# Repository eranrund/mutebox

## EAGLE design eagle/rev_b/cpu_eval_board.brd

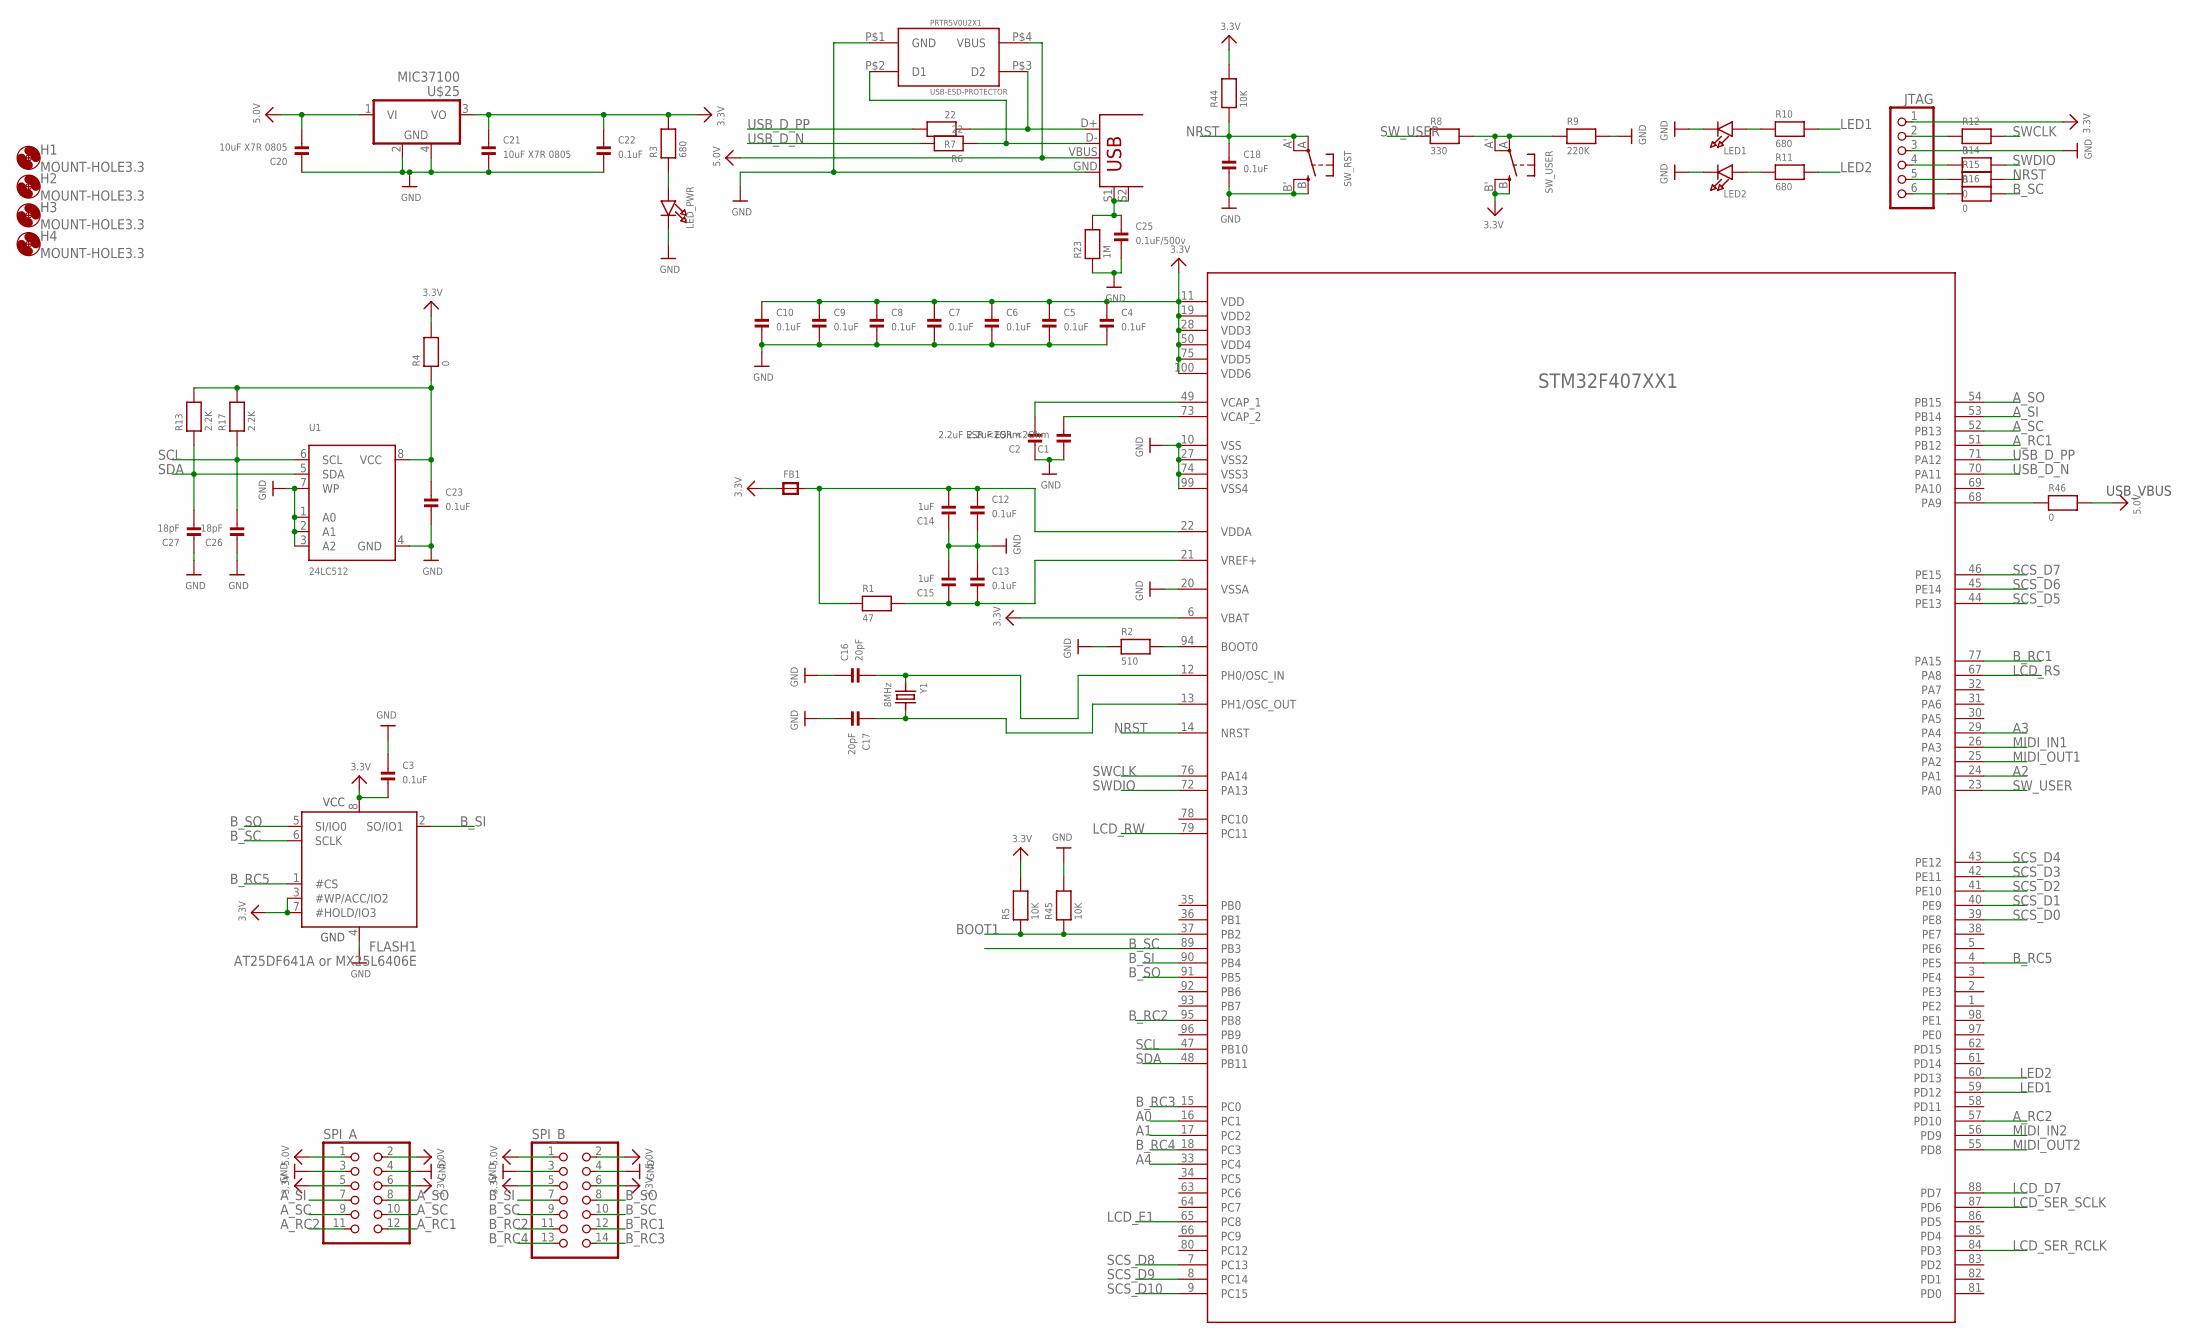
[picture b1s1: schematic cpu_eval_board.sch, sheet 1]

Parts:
C1, C2: 2.2uF ESR <2Ohm; 0603; PARTNO GRM188R61E225KA12D,Murata Electronics,,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
C3, C4, C5, C6, C7, C8, C9, C10, C12, C13, C18, C22, C23: 0.1uF; 0603; PARTNO VJ0603Y104JXJPW1BC,Vishay / Vitramon,,7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
C14, C15: 1uF; 0603; PARTNO GRM188R61E105KA12D,Murata Electronics,,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
C16, C17: 20pF; 0603; PARTNO GRM1885C1H200JA01D,Murata Electronics,,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
C20, C21: 10uF X7R 0805; _0805; PARTNO GRM21BR71A106KA73L,Murata Electronics,,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
C25: 0.1uF/500v; 0603; PARTNO CGA3E3X7S2A104M080AB,TDK,,810-CGA3E3X7S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
C26, C27: 18pF; 0603; PARTNO VJ0603A180JXACW1BC,Vishay / Vitramon,,7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
FB1: FERRITE_0805; _0805; PARTNO HZ0805E601R-10,Laird Technologies,,875-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
FLASH1: AT25DF641A or MX25L6406E; SOIC-8-WIDE
H1, H2, H3, H4: MOUNT-HOLE3.3; 3,3
JTAG: HEADER-1X6ROUND; 1X06_ROUND; PARTNO XG8V-0641,Omron Electronics,,653-XG8V-0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
LED1, LED2: LED0603; CHIPLED_0603; PARTNO VLMS1300-GS08,Vishay Semiconductors,,78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
LED_PWR: LED0603; CHIPLED_0603; PARTNO VLMS1300-GS08,Vishay Semiconductors,,78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
PRTR5V0U2X1: USB-ESD-PROTECTOR; PRTR5V0U2X; PARTNO PRTR5V0U2X,215",NXP Semiconductors,,771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
R1: 47; 0603; PARTNO CRCW060347R0FKEA,Vishay / Dale,,71-CRCW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
R2: 510; 0603; PARTNO RT0603FRE07510RL,Yageo,,603-RT0603FRE07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
R3, R10, R11: 680; 0603; PARTNO MCT06030C6800FP500,Vishay / Beyschlag,,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
R4, R12, R14, R15, R16, R46: 0; 0603; PARTNO MCT06030Z0000ZP500,Vishay / Beyschlag,,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
R5, R44, R45: 10K; 0603; PARTNO CRCW060310K0FKEA,Vishay / Dale,,71-CRCW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
R6, R7: 22; 0603; PARTNO MCT06030C2209FP500,Vishay / Beyschlag,,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
R8: 330; 0603; PARTNO RT0603FRE07330RL,Yageo,,603-RT0603FRE07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
R9: 220K; 0603; PARTNO RT0603FRE07220KL,Yageo,,603-RT0603FRE07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
R13, R17: 2.2K; 0603; PARTNO MCT06030C2201FP500,Vishay / Beyschlag,,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
R23: 1M; 0603; PARTNO CRCW06031M00FKEA,Vishay / Dale,,71-CRCW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
SPI_A: PINHD-2X6; 2X06; PARTNO 67996-412HLF,FCI,,649-67996-412HLF,6x2 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
SPI_B: PINHD-2X7; 2X07; PARTNO 67997-414HLF,FCI,,649-67997-414HLF,7x2 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
STM32F407XX1: STM32F407; 100LQFP; PARTNO STM32F407VGT6,ST,,511-STM32F407VGT6,ARM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
SW_RST: SWITCH_TACT_SMT; EVQ-Q2; PARTNO EVQ-PQHB55,Panasonic,,667-EVQ-PQHB55,Ta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
SW_USER: SWITCH_TACT_SMT; EVQ-Q2; PARTNO EVQ-PQHB55,Panasonic,,667-EVQ-PQHB55,Ta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
U1: 24LC512; SOIC8_150MIL; PARTNO 24LC512-I/SN,Microchip Technology,,579-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
U$14: Molex 67068-9001; USB-B-PTH; PARTNO 67068-9001,Molex,,538-67068-9001,USB Co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
U$25: MIC37100; SOT223; PARTNO MIC37100-3.3WS TR,Micrel,,998-MIC37100-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
Y1: 8MHz; HC49UP; PARTNO ABLS-8.000MHZ-B4-T,ABRACON,,815-ABLS-8.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

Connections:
3.3V: C3.2, C4.1, C5.1, C6.1, C7.1, C8.1, C9.1, C10.1, C21.1, C22.1, FB1.1, FLASH1.3 (#WP/ACC/IO2), FLASH1.7 (#HOLD/IO3), FLASH1.8 (VCC), JTAG.1, R3.2, R4.2, R5.2, R44.2, SPI_A.5, SPI_A.6, SPI_B.5, SPI_B.6, STM32F407XX1.6 (VBAT), STM32F407XX1.11 (VDD), STM32F407XX1.19 (VDD2), STM32F407XX1.28 (VDD3), STM32F407XX1.50 (VDD4), STM32F407XX1.75 (VDD5), STM32F407XX1.100 (VDD6), SW_USER.B (S), SW_USER.B' (S1), U$25.3 (VO); also elsewhere on the board
5.0V: C20.2, PRTR5V0U2X1.P$4 (VBUS), R46.2, SPI_A.1, SPI_A.2, SPI_B.1, SPI_B.2, U$14.VBUS, U$25.1 (VI); also elsewhere on the board
A0: STM32F407XX1.16 (PC1); also elsewhere on the board
A1: STM32F407XX1.17 (PC2); also elsewhere on the board
A2: STM32F407XX1.24 (PA1); also elsewhere on the board
A3: STM32F407XX1.29 (PA4); also elsewhere on the board
A4: STM32F407XX1.33 (PC4); also elsewhere on the board
A_RC1: SPI_A.12, STM32F407XX1.51 (PB12)
A_RC2: SPI_A.11, STM32F407XX1.57 (PD10)
A_SC: SPI_A.9, SPI_A.10, STM32F407XX1.52 (PB13)
A_SI: SPI_A.7, STM32F407XX1.53 (PB14)
A_SO: SPI_A.8, STM32F407XX1.54 (PB15)
BOOT1: R5.1, R45.1, STM32F407XX1.37 (PB2)
B_RC1: SPI_B.12, STM32F407XX1.77 (PA15)
B_RC2: SPI_B.11, STM32F407XX1.95 (PB8)
B_RC3: SPI_B.14, STM32F407XX1.15 (PC0)
B_RC4: SPI_B.13, STM32F407XX1.18 (PC3)
B_RC5: FLASH1.1 (#CS), STM32F407XX1.4 (PE5)
B_SC: FLASH1.6 (SCLK), R16.2, SPI_B.9, SPI_B.10, STM32F407XX1.89 (PB3)
B_SI: FLASH1.2 (SO/IO1), SPI_B.7, STM32F407XX1.90 (PB4)
B_SO: FLASH1.5 (SI/IO0), SPI_B.8, STM32F407XX1.91 (PB5)
GND: C1.1, C2.1, C3.1, C4.2, C5.2, C6.2, C7.2, C8.2, C9.2, C10.2, C12.2, C13.1, C14.1, C15.2, C16.1, C17.2, C18.2, C20.1, C21.2, C22.2, C23.2, C25.2, C26.1, C27.1, FLASH1.4 (GND), JTAG.3, LED1.C, LED2.C, LED_PWR.C, PRTR5V0U2X1.P$1 (GND), R2.1, R9.2, R23.1, R45.2, SPI_A.3, SPI_A.4, SPI_B.3, SPI_B.4, STM32F407XX1.10 (VSS), STM32F407XX1.20 (VSSA), STM32F407XX1.27 (VSS2), STM32F407XX1.74 (VSS3), STM32F407XX1.99 (VSS4), SW_RST.B (S), SW_RST.B' (S1), U1.1 (A0), U1.2 (A1), U1.3 (A2), U1.4 (GND), U1.7 (WP), U$14.GND, U$25.2 (GND), U$25.4 (GND_TAB); also elsewhere on the board
LCD_D7: STM32F407XX1.88 (PD7); also elsewhere on the board
LCD_E1: STM32F407XX1.65 (PC8); also elsewhere on the board
LCD_RS: STM32F407XX1.67 (PA8); also elsewhere on the board
LCD_RW: STM32F407XX1.79 (PC11); also elsewhere on the board
LCD_SER_RCLK: STM32F407XX1.84 (PD3); also elsewhere on the board
LCD_SER_SCLK: STM32F407XX1.87 (PD6); also elsewhere on the board
LED1: R10.2, STM32F407XX1.59 (PD12)
LED2: R11.2, STM32F407XX1.60 (PD13)
MIDI_IN1: STM32F407XX1.26 (PA3); also elsewhere on the board
MIDI_IN2: STM32F407XX1.56 (PD9); also elsewhere on the board
MIDI_OUT1: STM32F407XX1.25 (PA2); also elsewhere on the board
MIDI_OUT2: STM32F407XX1.55 (PD8); also elsewhere on the board
unnamed: C2.2, STM32F407XX1.49 (VCAP_1)
unnamed: C1.2, STM32F407XX1.73 (VCAP_2)
unnamed: R46.1, STM32F407XX1.68 (PA9)
unnamed: R2.2, STM32F407XX1.94 (BOOT0)
unnamed: C16.2, STM32F407XX1.12 (PH0/OSC_IN), Y1.1
unnamed: C23.1, R4.1, R13.2, R17.2, U1.8 (VCC)
unnamed: LED_PWR.A, R3.1
unnamed: C17.1, STM32F407XX1.13 (PH1/OSC_OUT), Y1.2
unnamed: PRTR5V0U2X1.P$2 (D1), R6.1, U$14.D-
unnamed: PRTR5V0U2X1.P$3 (D2), R7.1, U$14.D+
unnamed: R8.2, R9.1, SW_USER.A, SW_USER.A' (P1)
unnamed: LED1.A, R10.1
unnamed: LED2.A, R11.1
unnamed: JTAG.2, R12.1
unnamed: JTAG.4, R14.1
unnamed: JTAG.5, R15.1
unnamed: JTAG.6, R16.1
unnamed: C25.1, R23.2, U$14.S1, U$14.S2
NRST: C18.1, R15.2, R44.1, STM32F407XX1.14 (NRST), SW_RST.A, SW_RST.A' (P1)
SCL: C26.2, R17.1, STM32F407XX1.47 (PB10), U1.6 (SCL)
SCS_D0: STM32F407XX1.39 (PE8); also elsewhere on the board
SCS_D1: STM32F407XX1.40 (PE9); also elsewhere on the board
SCS_D2: STM32F407XX1.41 (PE10); also elsewhere on the board
SCS_D3: STM32F407XX1.42 (PE11); also elsewhere on the board
SCS_D4: STM32F407XX1.43 (PE12); also elsewhere on the board
SCS_D5: STM32F407XX1.44 (PE13); also elsewhere on the board
SCS_D6: STM32F407XX1.45 (PE14); also elsewhere on the board
SCS_D7: STM32F407XX1.46 (PE15); also elsewhere on the board
SCS_D8: STM32F407XX1.7 (PC13); also elsewhere on the board
SCS_D9: STM32F407XX1.8 (PC14); also elsewhere on the board
SCS_D10: STM32F407XX1.9 (PC15); also elsewhere on the board
SDA: C27.2, R13.1, STM32F407XX1.48 (PB11), U1.5 (SDA)
SWCLK: R12.2, STM32F407XX1.76 (PA14)
SWDIO: R14.2, STM32F407XX1.72 (PA13)
SW_USER: R8.1, STM32F407XX1.23 (PA0)
USB_D_N: R6.2, STM32F407XX1.70 (PA11)
USB_D_PP: R7.2, STM32F407XX1.71 (PA12)
VDDA: C12.1, C14.2, FB1.2, R1.1, STM32F407XX1.22 (VDDA)
VREF: C13.2, C15.1, R1.2, STM32F407XX1.21 (VREF+)

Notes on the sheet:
USB_VBUS

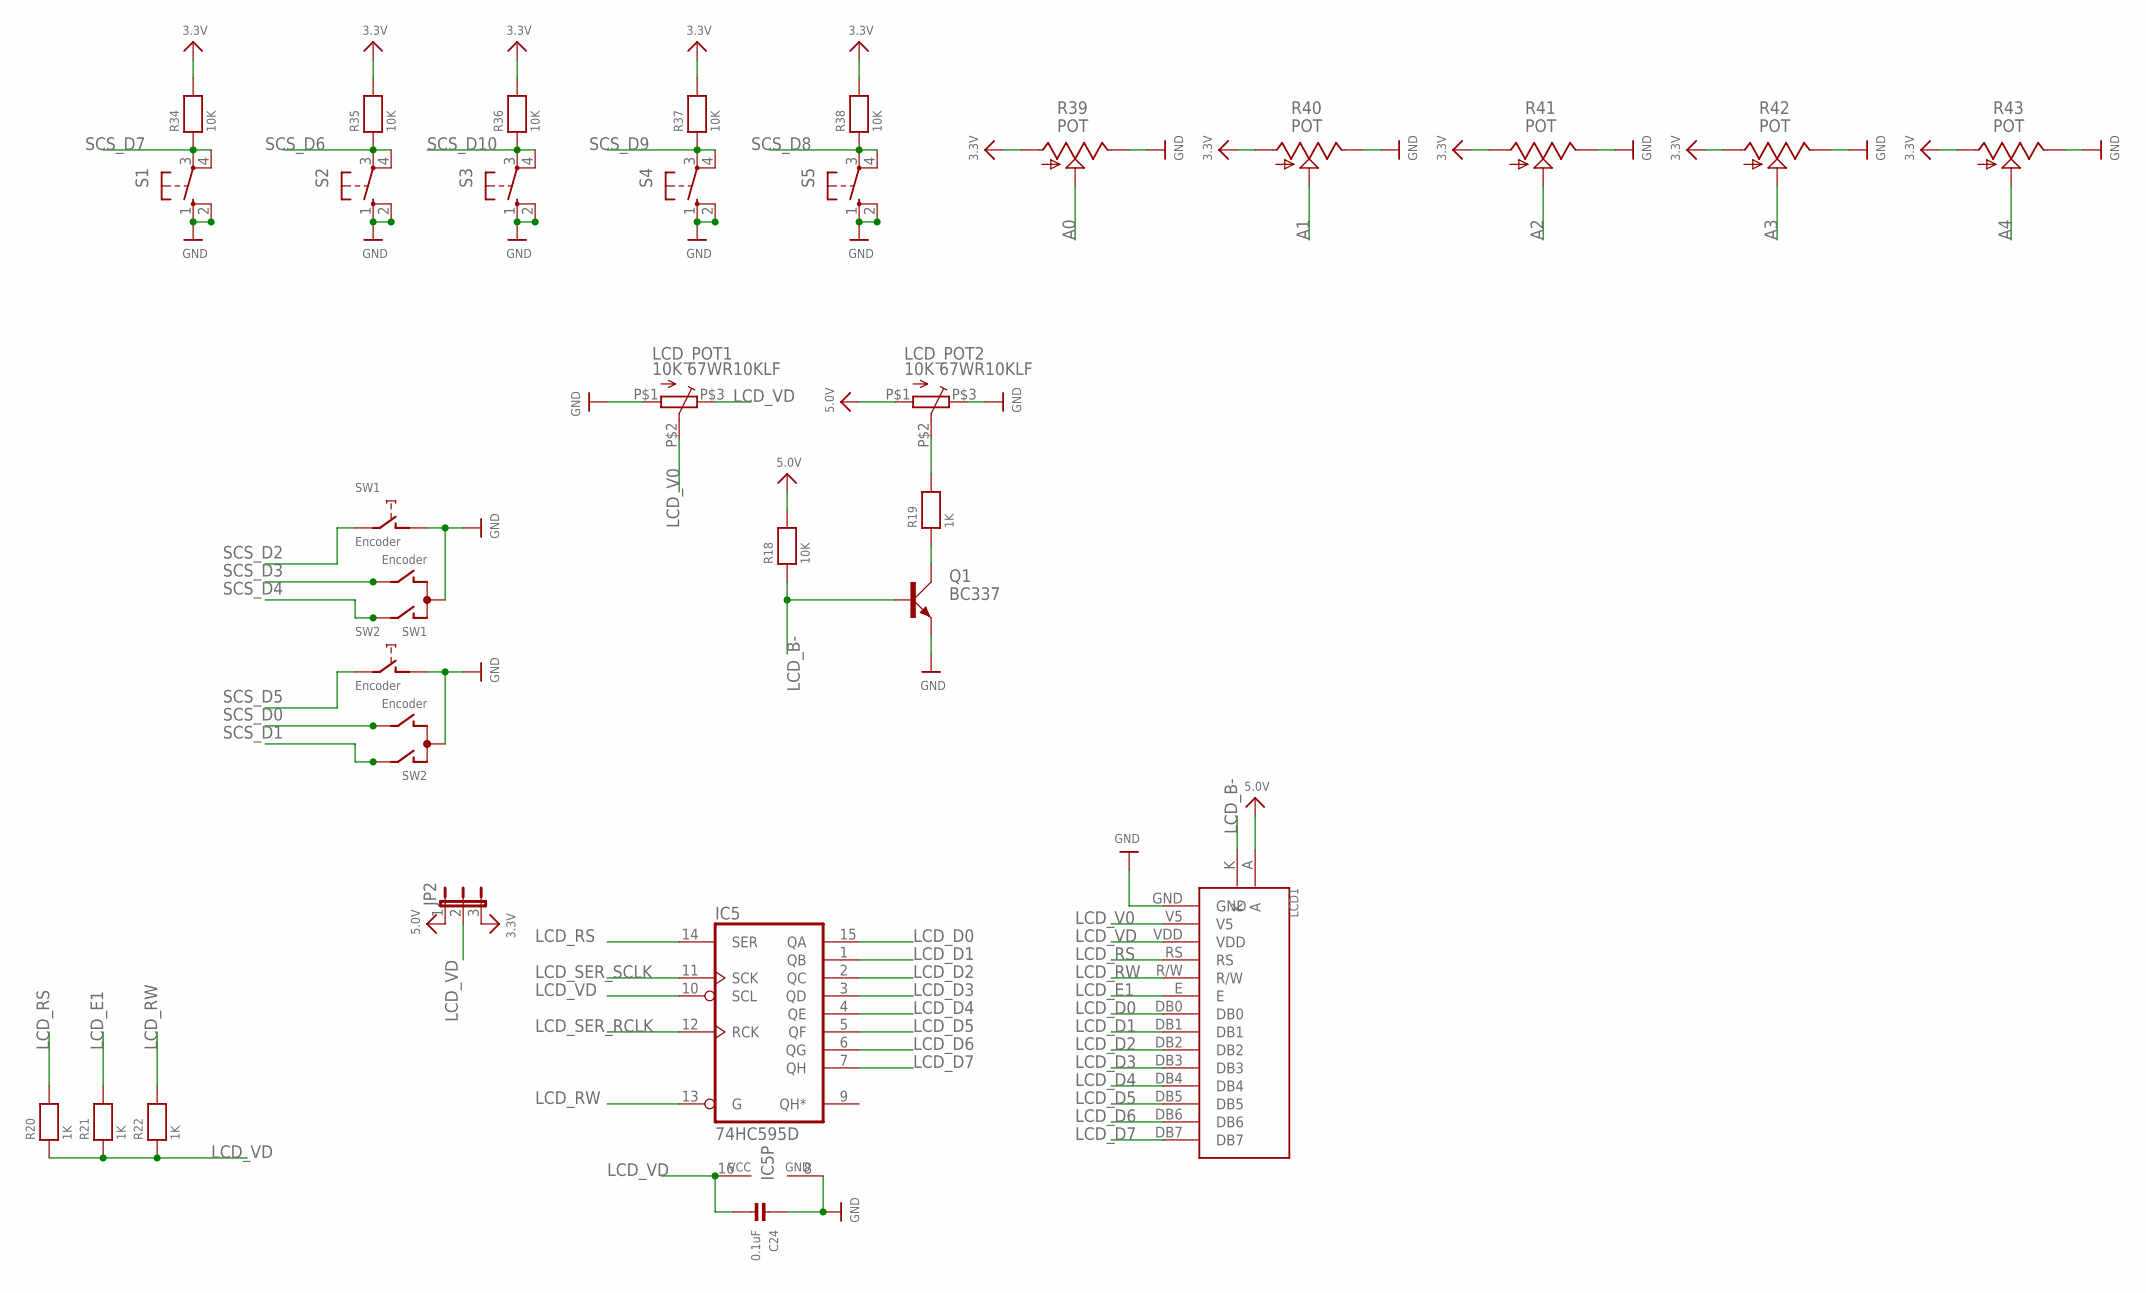
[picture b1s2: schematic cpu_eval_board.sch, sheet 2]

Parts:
C24: 0.1uF; 0603; PARTNO VJ0603Y104JXJPW1BC,Vishay / Vitramon,,7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
IC5: 74HC595D; SO16; PARTNO 74HC595D,NXP Semiconductors,,771-74HC59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
JP2: JUMPER3; PARTNO 4-103327-5,TE Connectivity / AMP,,571-4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
LCD1: NHD-C0220AA-FSW-FTW; PARTNO NHD-C0220AA-FSW-FTW,Newhaven Display,,7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
LCD_POT1, LCD_POT2: 10K 67WR10KLF; 67W; PARTNO 67WR10KLF,BI Technologies / TT Electron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
Q1: BC337; SOT54A; PARTNO BC337-16 A1,Taiwan ,,821-BC337-16-A1,Bi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
R18, R34, R35, R36, R37, R38: 10K; _0603; PARTNO CRCW060310K0FKEA,Vishay / Dale,,71-CRCW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
R19, R20, R21, R22: 1K; _0603; PARTNO CRCW06031K00FKEA,Vishay / Dale,,71-CRCW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
R39, R40, R41, R42, R43: POT; ALPS_POT_SFE; PARTNO RK09D1130C2P,ALPS,,688-RK09D1130C2P,Pot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
S1, S2, S3, S4, S5: 40-XX; B3F-40XX; PARTNO TL1100F160Q,E-Switch,,612-TL1100,Tactil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
SW1, SW2: Encoder; ALPS_EC12E_SW; PARTNO RK09D1130C2P,ALPS,,688-RK09D1130C2P,Pot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

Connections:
3.3V: JP2.3, R34.2, R35.2, R36.2, R37.2, R38.2, R39.P$3 (A), R40.P$3 (A), R41.P$3 (A), R42.P$3 (A), R43.P$3 (A); also elsewhere on the board
5.0V: JP2.1, LCD1.A, LCD_POT2.P$1 (A), R18.2; also elsewhere on the board
A0: R39.P$2 (S); also elsewhere on the board
A1: R40.P$2 (S); also elsewhere on the board
A2: R41.P$2 (S); also elsewhere on the board
A3: R42.P$2 (S); also elsewhere on the board
A4: R43.P$2 (S); also elsewhere on the board
GND: C24.1, IC5.8 (GND), LCD1.GND, LCD_POT1.P$1 (A), LCD_POT2.P$3 (E), Q1.E, R39.P$1 (E), R40.P$1 (E), R41.P$1 (E), R42.P$1 (E), R43.P$1 (E), S1.1 (S), S1.2 (S1), S2.1 (S), S2.2 (S1), S3.1 (S), S3.2 (S1), S4.1 (S), S4.2 (S1), S5.1 (S), S5.2 (S1), SW1.C, SW1.D (1), SW2.C, SW2.D (1); also elsewhere on the board
LCD_B-: LCD1.K, Q1.B, R18.1
LCD_D0: IC5.15 (QA), LCD1.DB0
LCD_D1: IC5.1 (QB), LCD1.DB1
LCD_D2: IC5.2 (QC), LCD1.DB2
LCD_D3: IC5.3 (QD), LCD1.DB3
LCD_D4: IC5.4 (QE), LCD1.DB4
LCD_D5: IC5.5 (QF), LCD1.DB5
LCD_D6: IC5.6 (QG), LCD1.DB6
LCD_D7: IC5.7 (QH), LCD1.DB7; also elsewhere on the board
LCD_E1: LCD1.E, R21.2; also elsewhere on the board
LCD_RS: IC5.14 (SER), LCD1.RS, R20.2; also elsewhere on the board
LCD_RW: IC5.13 (G), LCD1.R/W, R22.2; also elsewhere on the board
LCD_SER_RCLK: IC5.12 (RCK); also elsewhere on the board
LCD_SER_SCLK: IC5.11 (SCK); also elsewhere on the board
LCD_V0: LCD1.V5, LCD_POT1.P$2 (S)
LCD_VD: C24.2, IC5.10 (SCL), IC5.16 (VCC), JP2.2, LCD1.VDD, LCD_POT1.P$3 (E), R20.1, R21.1, R22.1
unnamed: Q1.C, R19.1
unnamed: LCD_POT2.P$2 (S), R19.2
SCS_D0: SW2.B; also elsewhere on the board
SCS_D1: SW2.A; also elsewhere on the board
SCS_D2: SW1.E (2); also elsewhere on the board
SCS_D3: SW1.B; also elsewhere on the board
SCS_D4: SW1.A; also elsewhere on the board
SCS_D5: SW2.E (2); also elsewhere on the board
SCS_D6: R35.1, S2.3, S2.4 (P1); also elsewhere on the board
SCS_D7: R34.1, S1.3, S1.4 (P1); also elsewhere on the board
SCS_D8: R38.1, S5.3, S5.4 (P1); also elsewhere on the board
SCS_D9: R37.1, S4.3, S4.4 (P1); also elsewhere on the board
SCS_D10: R36.1, S3.3, S3.4 (P1); also elsewhere on the board

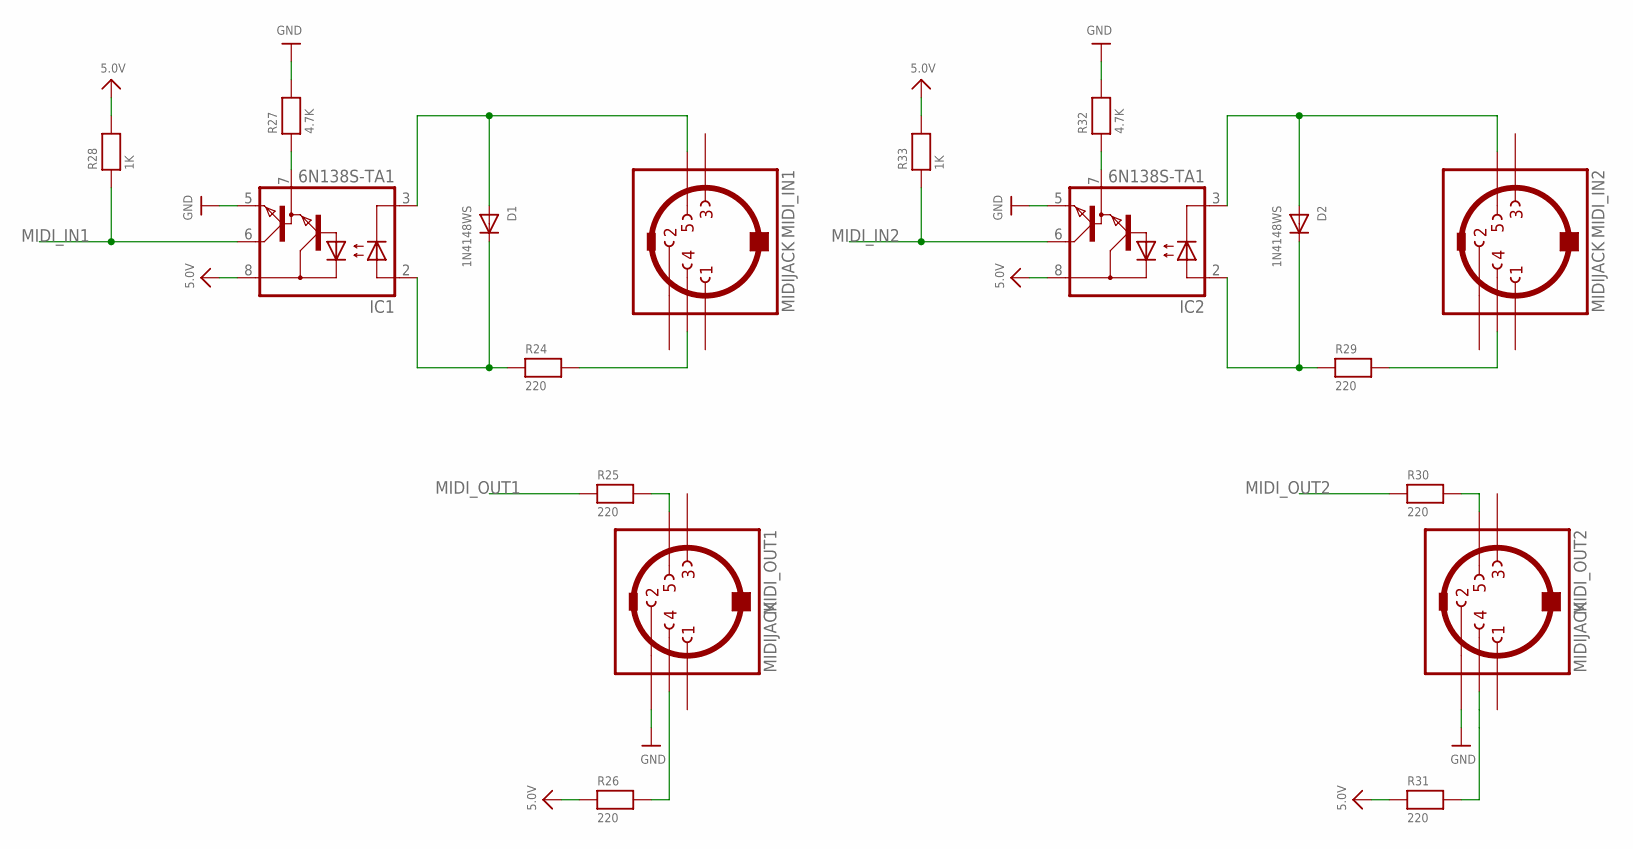
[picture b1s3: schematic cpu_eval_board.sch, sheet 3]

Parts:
D1, D2: 1N4148WS; SOD-323; PARTNO 1N4148WSFL-G3-08,Vishay Semiconductors,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
IC1, IC2: 6N138S-TA1; SO8-GW300; PARTNO 6N138S-TA1,Lite-On,,859-6N138STA1,High 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
MIDI_IN1, MIDI_IN2: MIDIJACK; CP-2350; PARTNO 57PC5F,Switchcraft,,502-57PC5F,DIN Conn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
MIDI_OUT1, MIDI_OUT2: MIDIJACK; CP-2350; PARTNO 57PC5F,Switchcraft,,502-57PC5F,DIN Conn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
R24, R25, R26, R29, R30, R31: 220; _0603; PARTNO MCT06030C2200FP500,Vishay / Beyschlag,,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
R27, R32: 4.7K; _0603; PARTNO MCT06030C4701FP500,Vishay,,594-MCT06030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
R28, R33: 1K; _0603; PARTNO CRCW06031K00FKEA,Vishay / Dale,,71-CRCW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

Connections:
5.0V: IC1.8 (VCC), IC2.8 (VCC), R26.1, R28.2, R31.1, R33.2; also elsewhere on the board
GND: IC1.5 (GND), IC2.5 (GND), MIDI_OUT1.2, MIDI_OUT2.2, R27.2, R32.2; also elsewhere on the board
MIDI_IN1: IC1.6 (VO), R28.1; also elsewhere on the board
MIDI_IN2: IC2.6 (VO), R33.1; also elsewhere on the board
MIDI_OUT1: R25.1; also elsewhere on the board
MIDI_OUT2: R30.1; also elsewhere on the board
unnamed: MIDI_OUT1.5, R25.2
unnamed: MIDI_OUT1.4, R26.2
unnamed: MIDI_IN1.4, R24.2
unnamed: D1.C, IC1.2 (A), R24.1
unnamed: D1.A, IC1.3 (C), MIDI_IN1.5
unnamed: IC1.7 (VB), R27.1
unnamed: MIDI_OUT2.5, R30.2
unnamed: MIDI_OUT2.4, R31.2
unnamed: MIDI_IN2.4, R29.2
unnamed: D2.C, IC2.2 (A), R29.1
unnamed: D2.A, IC2.3 (C), MIDI_IN2.5
unnamed: IC2.7 (VB), R32.1

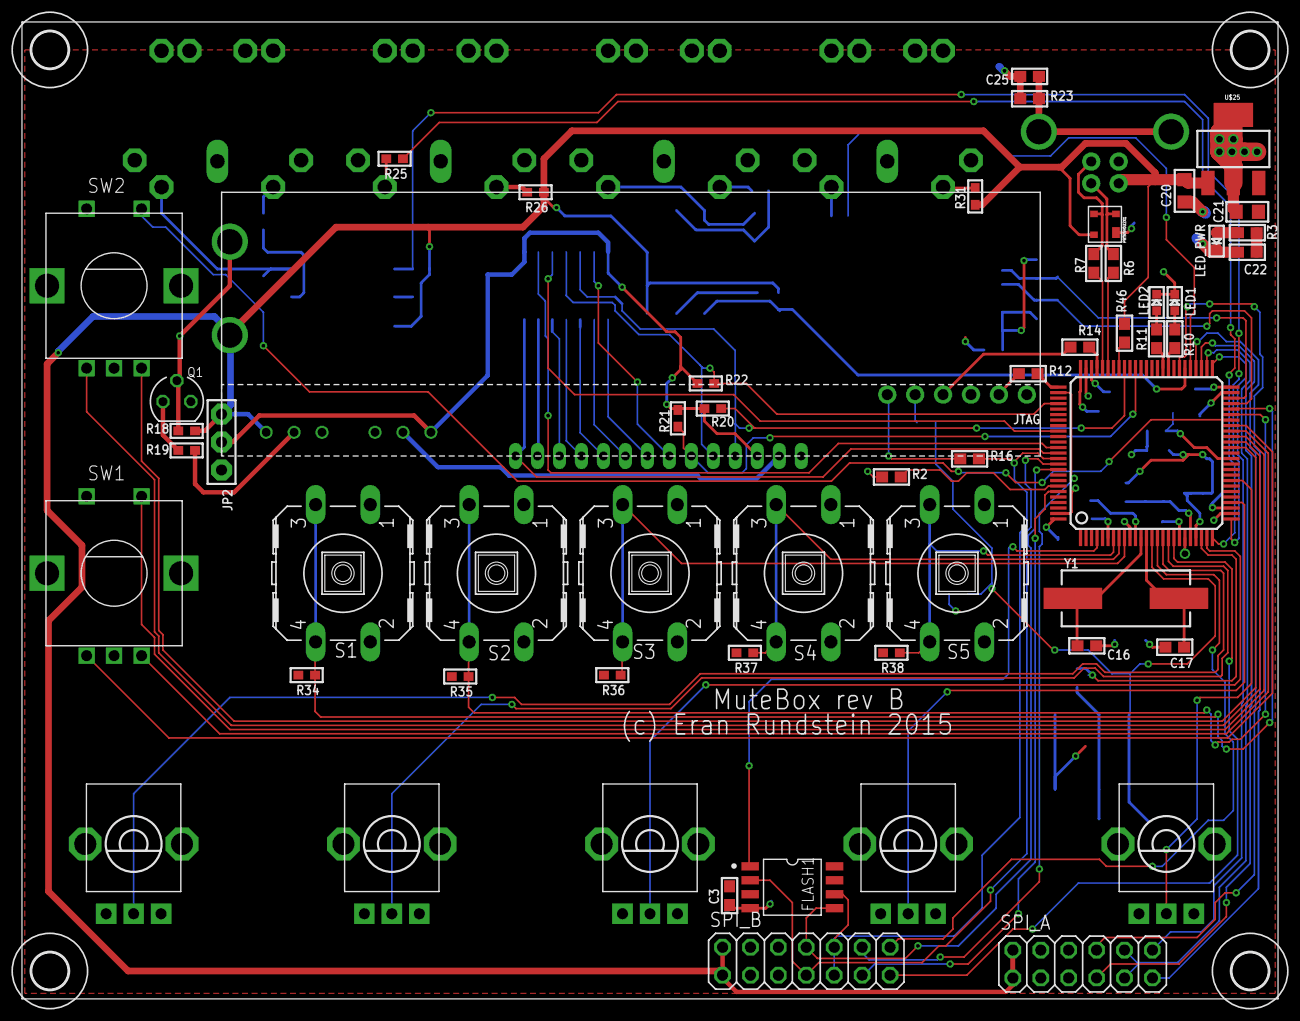
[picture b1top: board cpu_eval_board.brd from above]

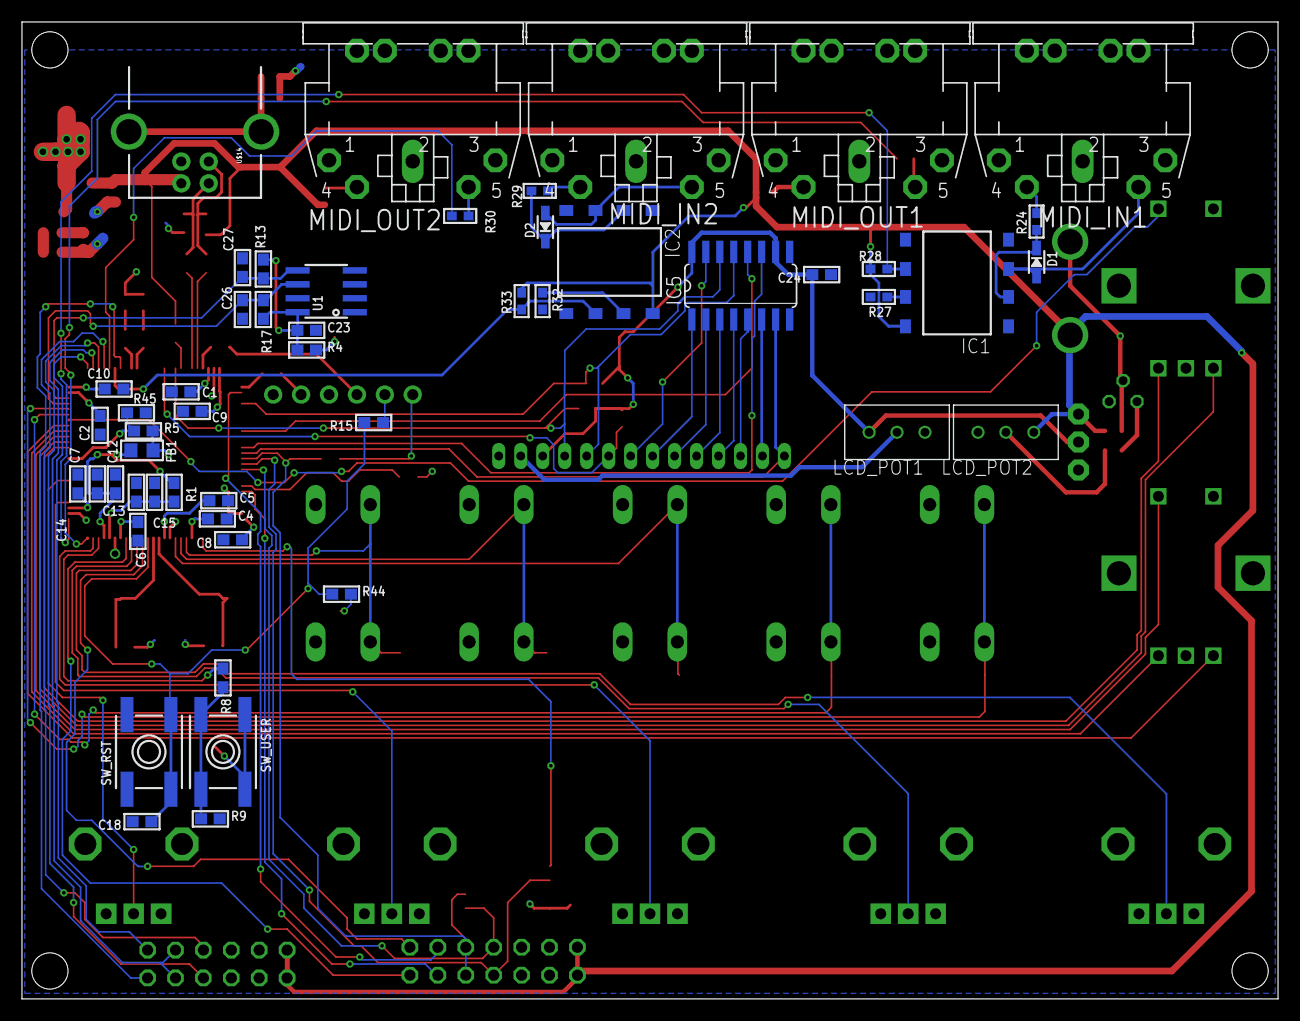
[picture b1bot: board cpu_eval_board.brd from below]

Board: 2 copper layers, 114.3 x 88.9 mm, 112 parts (51 on the bottom side), 97 nets.

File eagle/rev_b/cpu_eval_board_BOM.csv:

Qty-1,Part References,Value,Package,Mfg Part Num,Mfg Name,VID,Vendor Part Num,Description,Pkg Code,XREF
1,"JP2",,JUMPER3,***PART# '4-103327-5,TE CONNECTIVITY / AMP,,571-4-103327-5,3 PIN HEADER 1 ROW, REF3' NOT FOUND***,*
1,"SPI_A",,2X06,***PART# '67996-412HLF,FCI,,649-67996-412HLF,6X2 HEADER PINS, REF4' NOT FOUND***,*
1,"SPI_B",,2X07,***PART# '67997-414HLF,FCI,,649-67997-414HLF,7X2 HEADER PINS, REF5' NOT FOUND***,*
2,"SW_RST, SW_USER",,EVQ-Q2,***PART# 'EVQ-PQHB55,PANASONIC,,667-EVQ-PQHB55,TACTILE SWITCHES SUPER SMALL SIZED S LIGHT TOUCH SWITCH, REF21' NOT FOUND***,*
1,"FB1",,_0805,***PART# 'HZ0805E601R-10,LAIRD TECHNOLOGIES,,875-HZ0805E601R-10,"EMI FILTER BEADS, CHIPS & ARRAYS 600OHMS 100MHZ .5A MONOLITHIC 0805 SMD",0805 REF1' NOT FOUND***,*
1,"STM32F407XX1",,100LQFP,***PART# 'STM32F407VGT6,ST,,511-STM32F407VGT6,ARM MICROCONTROLLERS - MCU ARM M4 1024 FLASH 168 MHZ 192KB SRAM, REF6' NOT FOUND***,*
5,"S1, S2, S3, S4, S5",,B3F-40XX,***PART# 'TL1100F160Q,E-SWITCH,,612-TL1100,TACTILE SWITCHES 12X7.3MM 160GF, REF38' NOT FOUND***,*
3,"LED1, LED2, LED_PWR",,CHIPLED_0603,***PART# 'VLMS1300-GS08,VISHAY SEMICONDUCTORS,,78-VLMS1300-GS08,STANDARD LEDS - SMD SUPER RED CLEAR NON-DIFF, REF34' NOT FOUND***,*
1,"JTAG",,1X06_ROUND,***PART# 'XG8V-0641,OMRON ELECTRONICS,,653-XG8V-0641,6 PIN HEADER 1 ROW, REF2' NOT FOUND***,*
6,"R4, R12, R14, R15, R16, R46",0,0603,***PART# 'MCT06030Z0000ZP500,VISHAY / BEYSCHLAG,,594-MCT06030Z0000ZP5,THIN FILM RESISTORS - SMD ZERO OHM JUMPER, REF40' NOT FOUND***,*
14,"C3, C4, C5, C6, C7, C8, C9, C10, C12, C13, C18, C22, C23, C24",0.1uF,0603,***PART# 'VJ0603Y104JXJPW1BC,VISHAY / VITRAMON,,77-VJ0603Y104JXJPBC,MULTILAYER CERAMIC CAPACITORS MLCC - SMD/SMT 0603 0.1UF 16VOLTS X7R 5%, REF44' NOT FOUND***,*
1,"C25",0.1uF/500v,0603,***PART# 'CGA3E3X7S2A104M080AB,TDK,,810-CGA3E3X7S2A104AB,MULTILAYER CERAMIC CAPACITORS MLCC - SMD/SMT .1UF 100V 20% 0603, REF7' NOT FOUND***,*
6,"R19, R20, R21, R22, R28, R33",1K,_0603,***PART# 'CRCW06031K00FKEA,VISHAY / DALE,,71-CRCW0603-1.0K-E3,THICK FILM RESISTORS - SMD 1/10WATT 1.0KOHMS 1%, REF41' NOT FOUND***,*
1,"R23",1M,0603,***PART# 'CRCW06031M00FKEA,VISHAY / DALE,,71-CRCW0603-1.0M-E3,THICK FILM RESISTORS - SMD 1/10WATT 1.0MOHMS 1%, REF8' NOT FOUND***,*
2,"D1, D2",1N4148WS,SOD-323,***PART# '1N4148WSFL-G3-08,VISHAY SEMICONDUCTORS,,78-1N4148WSFL-G3-08,"DIODES - GENERAL PURPOSE, POWER, SWITCHING 100VOLT 350MA 4NS", REF22' NOT FOUND***,*
2,"C14, C15",1uF,0603,***PART# 'GRM188R61E105KA12D,MURATA ELECTRONICS,,81-GRM188R61E105KA12,MULTILAYER CERAMIC CAPACITORS MLCC - SMD/SMT 0603 1UF 25VOLTS X5R 10%, REF23' NOT FOUND***,*
2,"R13, R17",2.2K,0603,***PART# 'MCT06030C2201FP500,VISHAY / BEYSCHLAG,,594-MCT06030C2201FP5,THIN FILM RESISTORS - SMD .1W 2.2KOHM 1% 0603 50PPM AUTO, REF24' NOT FOUND***,*
2,"C1, C2",2.2uF ESR <2Ohm,0603,***PART# 'GRM188R61E225KA12D,MURATA ELECTRONICS,,81-GRM188R61E225KA2D,MULTILAYER CERAMIC CAPACITORS MLCC - SMD/SMT 0603 2.2UF 25VOLTS X5R 10%, REF25' NOT FOUND***,*
2,"R27, R32",4.7K,_0603,***PART# 'MCT06030C4701FP500,VISHAY,,594-MCT06030C4701FP5,THIN FILM RESISTORS - SMD .1W 4.7KOHMS 1% 0603 50PPM AUTO, REF26' NOT FOUND***,*
2,"IC1, IC2",6N138S-TA1,SO8-GW300,***PART# '6N138S-TA1,LITE-ON,,859-6N138STA1,HIGH SPEED OPTOCOUPLERS DARLINGTON 100KBD TRANSISTOR OUTPUT, REF27' NOT FOUND***,*
1,"Y1",8MHz,HC49UP,***PART# 'ABLS-8.000MHZ-B4-T,ABRACON,,815-ABLS-8.0M-T,CRYSTALS 8.000MHZ 30PPM -20C +70C 18PF, REF9' NOT FOUND***,*
3,"R5, R44, R45",10K,0603,***PART# 'CRCW060310K0FKEA,VISHAY / DALE,,71-CRCW0603-10K-E3,THICK FILM RESISTORS - SMD 1/10WATT 10KOHMS 1%, REF35' NOT FOUND***,*
6,"R18, R34, R35, R36, R37, R38",10K,_0603,***PART# 'CRCW060310K0FKEA,VISHAY / DALE,,71-CRCW0603-10K-E3,THICK FILM RESISTORS - SMD 1/10WATT 10KOHMS 1%, REF35' NOT FOUND***,*
2,"LCD_POT1, LCD_POT2",10K 67WR10KLF,67W,***PART# '67WR10KLF,BI TECHNOLOGIES / TT ELECTRONICS,,858-67WR10KLF,"TRIMMER RESISTORS - THROUGH HOLE 3/8"" SQU 10K 10%", REF28' NOT FOUND***,*
2,"C20, C21",10uF X7R 0805,_0805,***PART# 'GRM21BR71A106KA73L,MURATA ELECTRONICS,,81-GRM21BR71A106KA3L,MULTILAYER CERAMIC CAPACITORS MLCC - SMD/SMT 0805 10UF 10VOLTS X7R + - 10%, REF29' NOT FOUND***,*
2,"C26, C27",18pF,0603,***PART# 'VJ0603A180JXACW1BC,VISHAY / VITRAMON,,77-VJ0603A180JXACBC,MULTILAYER CERAMIC CAPACITORS MLCC - SMD/SMT 0603 18PF 50VOLTS C0G 5%, REF30' NOT FOUND***,*
2,"C16, C17",20pF,0603,***PART# 'GRM1885C1H200JA01D,MURATA ELECTRONICS,,81-GRM39C200J50,MULTILAYER CERAMIC CAPACITORS MLCC - SMD/SMT 0603 20PF 50VOLTS C0G 5%, REF31' NOT FOUND***,*
2,"R6, R7",22,0603,***PART# 'MCT06030C2209FP500,VISHAY / BEYSCHLAG,,594-MCT06030C2209FP5,THIN FILM RESISTORS - SMD .1W 22OHM 1% 0603 50PPM AUTO, REF32' NOT FOUND***,*
1,"U1",24LC512,SOIC8_150MIL,***PART# '24LC512-I/SN,MICROCHIP TECHNOLOGY,,579-24LC512-I/SN,EEPROM 512K 64K X 8 2.5V SER EE IND, REF10' NOT FOUND***,*
1,"R1",47,0603,***PART# 'CRCW060347R0FKEA,VISHAY / DALE,,71-CRCW0603-47-E3,THICK FILM RESISTORS - SMD 1/10WATT 47OHMS 1%, REF11' NOT FOUND***,*
1,"IC5",74HC595D,SO16,***PART# '74HC595D,NXP SEMICONDUCTORS,,771-74HC595D-T,COUNTER SHIFT REGISTERS 8-BIT SHIFT REG W/OUTPUT LATCH, REF12' NOT FOUND***,*
6,"R24, R25, R26, R29, R30, R31",220,_0603,***PART# 'MCT06030C2200FP500,VISHAY / BEYSCHLAG,,594-MCT06030C2200FP5,THIN FILM RESISTORS - SMD .1W 220OHM 1% 0603 50PPM AUTO, REF43' NOT FOUND***,*
1,"R9",220K,0603,***PART# 'RT0603FRE07220KL,YAGEO,,603-RT0603FRE07220KL,THIN FILM RESISTORS - SMD 1/10W 220K OHM 1% 50PPM, REF13' NOT FOUND***,*
1,"R8",330,0603,***PART# 'RT0603FRE07330RL,YAGEO,,603-RT0603FRE07330RL,THIN FILM RESISTORS - SMD 1/10W 330 OHM 1% 50PPM, REF14' NOT FOUND***,*
1,"R2",510,0603,***PART# 'RT0603FRE07510RL,YAGEO,,603-RT0603FRE07510RL,THIN FILM RESISTORS - SMD 1/10W 510 OHM 1% 50PPM, REF15' NOT FOUND***,*
3,"R3, R10, R11",680,0603,***PART# 'MCT06030C6800FP500,VISHAY / BEYSCHLAG,,594-MCT06030C6800FP5,THIN FILM RESISTORS - SMD .1W 680OHM 1% 0603 50PPM AUTO, REF36' NOT FOUND***,*
1,"FLASH1",AT25DF641A or MX25L6406E,SOIC-8-WIDE,***PART# '*' NOT FOUND***,*
1,"Q1",BC337,SOT54A,***PART# 'BC337-16 A1,TAIWAN ,,821-BC337-16-A1,BIPOLAR TRANSISTORS - BJT NPN TRANSISTOR, REF16' NOT FOUND***,*
2,"SW1, SW2",Encoder,ALPS_EC12E_SW,***PART# 'RK09D1130C2P,ALPS,,688-RK09D1130C2P,POTENTIOMETERS 9MM 10K V/ADJ, REF39' NOT FOUND***,*
1,"U$25",MIC37100,SOT223,***PART# 'MIC37100-3.3WS TR,MICREL,,998-MIC37100-3.3WSTR,LDO VOLTAGE REGULATORS 1.0A LOW VOLTAGE UCAP LDO REGULATOR IN SOT223 PKG(ROHS COMPLIANT), REF17' NOT FOUND***,*
4,"MIDI_IN1, MIDI_IN2, MIDI_OUT1, MIDI_OUT2",MIDIJACK,CP-2350,***PART# '57PC5F,SWITCHCRAFT,,502-57PC5F,DIN CONNECTORS 5 COND 180 DIN CONN, REF37' NOT FOUND***,*
4,"H1, H2, H3, H4",MOUNT-HOLE3.3,3,3,***PART# '*' NOT FOUND***,*
1,"U$14",Molex 67068-9001,USB-B-PTH,***PART# '67068-9001,MOLEX,,538-67068-9001,USB CONNECTORS USB TYPE B RECEPT R/A W/ SOLDER TABS, REF18' NOT FOUND***,*
1,"LCD1",NHD-C0220AA-FSW-FTW,NHD-C0220AA-FSW-FTW,***PART# 'NHD-C0220AA-FSW-FTW,NEWHAVEN DISPLAY,,763-C0220AA-FSW-FTW,LCD CHARACTER DISPLAY MODULES & ACCESSORIES COG FSTN(+) 2X20 WHITE TRANSFLECTIVE, REF19' NOT FOUND***,*
5,"R39, R40, R41, R42, R43",POT,ALPS_POT_SFE,***PART# 'RK09D1130C2P,ALPS,,688-RK09D1130C2P,POTENTIOMETERS 9MM 10K V/ADJ, REF39' NOT FOUND***,*
1,"PRTR5V0U2X1",USB-ESD-PROTECTOR,PRTR5V0U2X,***PART# 'PRTR5V0U2X,215",NXP SEMICONDUCTORS,,771-PRTR5V0U2X-T/R,ESD SUPPRESSORS 5.5V DUAL R-R ESD ULTRA LOW CAP, REF20' NOT FOUND***,*

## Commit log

2014-11-25 Import mios32 repo from svn://midibox.org/mios32 (rev 2093)
2014-11-25 initial skeleton
2014-12-28 osx lcd
2014-12-29 eeprom sux
2014-12-30 add seq
2014-12-31 seqseq
2014-12-31 has save
2014-12-31 patches
2015-02-18 cpu eval board wip
2015-03-06 routed
2015-03-08 all routed
2015-03-08 layout opt
2015-03-13 before silkscreen edits
2015-03-13 silkscreen edited
2015-03-25 lcd library edit
2015-03-28 cpu_eval_board rev b sent to oshpark

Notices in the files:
parts and their libraries:
microbuilder: This work is placed in the public domain, and may be freely used for commercial and non-commercial work with the following conditions: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
SparkFun-Connectors: Licensing: Creative Commons ShareAlike 4.0 International - https://creativecommons.org/licenses/by-sa/4.0
